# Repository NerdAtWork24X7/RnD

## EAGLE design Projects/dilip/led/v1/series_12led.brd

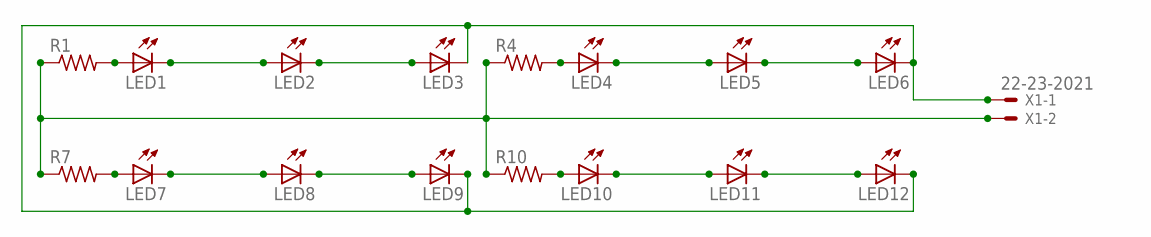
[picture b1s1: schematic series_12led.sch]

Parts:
LED1, LED2, LED3, LED4, LED5, LED6, LED7, LED8, LED9, LED10, LED11, LED12: LED3MM
R1, R4, R7, R10: R-US_0207/10; 0207/10
X1: 22-23-2021

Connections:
unnamed: R1.1, R4.1, R7.1, R10.1, X1.2
unnamed: LED1.A, R1.2
unnamed: LED1.K (C), LED2.A
unnamed: LED2.K (C), LED3.A
unnamed: LED4.A, R4.2
unnamed: LED4.K (C), LED5.A
unnamed: LED5.K (C), LED6.A
unnamed: LED7.A, R7.2
unnamed: LED7.K (C), LED8.A
unnamed: LED8.K (C), LED9.A
unnamed: LED10.A, R10.2
unnamed: LED10.K (C), LED11.A
unnamed: LED11.K (C), LED12.A
unnamed: LED3.K (C), LED6.K (C), LED9.K (C), LED12.K (C), X1.1

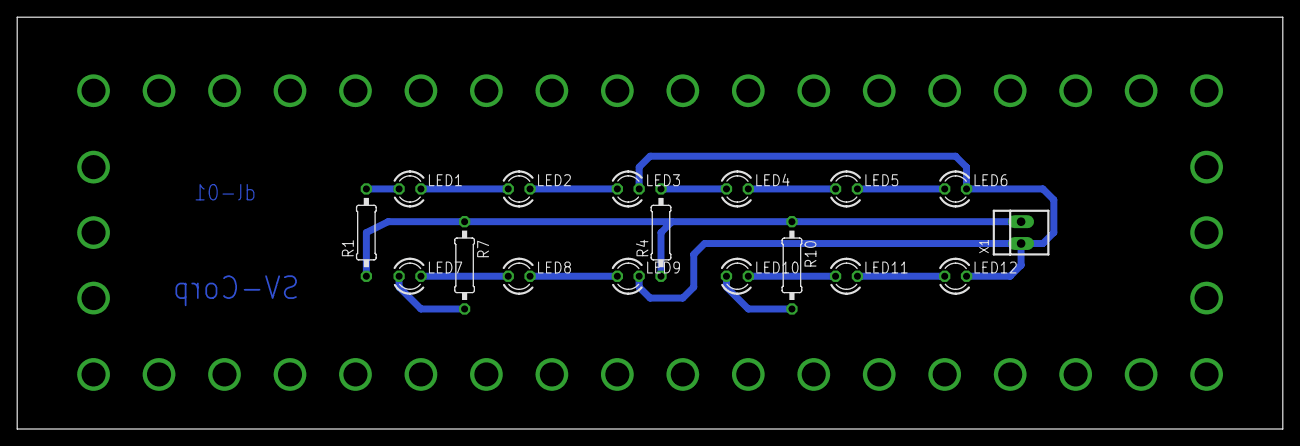
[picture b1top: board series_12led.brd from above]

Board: 2 copper layers, 147.3 x 47.9 mm, 17 parts (0 on the bottom side), 14 nets.

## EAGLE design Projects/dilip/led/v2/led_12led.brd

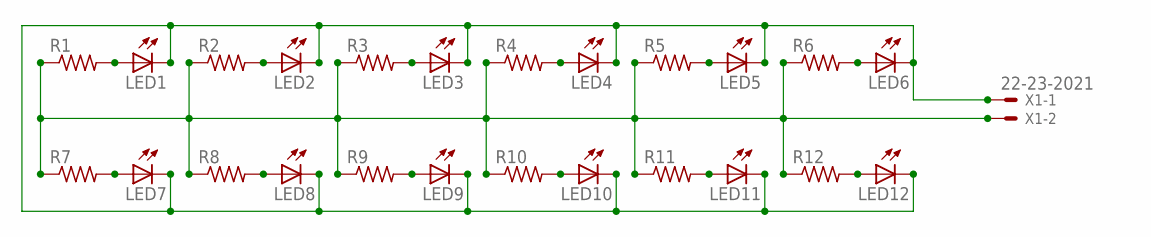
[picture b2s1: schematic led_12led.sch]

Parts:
LED1, LED2, LED3, LED4, LED5, LED6, LED7, LED8, LED9, LED10, LED11, LED12: LED3MM
R1, R2, R3, R4, R5, R6, R7, R8, R9, R10, R11, R12: R-US_0309/12; 0309/12
X1: 22-23-2021

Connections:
unnamed: R1.1, R2.1, R3.1, R4.1, R5.1, R6.1, R7.1, R8.1, R9.1, R10.1, R11.1, R12.1, X1.2
unnamed: LED1.A, R1.2
unnamed: LED2.A, R2.2
unnamed: LED3.A, R3.2
unnamed: LED4.A, R4.2
unnamed: LED5.A, R5.2
unnamed: LED6.A, R6.2
unnamed: LED7.A, R7.2
unnamed: LED8.A, R8.2
unnamed: LED9.A, R9.2
unnamed: LED10.A, R10.2
unnamed: LED11.A, R11.2
unnamed: LED12.A, R12.2
unnamed: LED1.K (C), LED2.K (C), LED3.K (C), LED4.K (C), LED5.K (C), LED6.K (C), LED7.K (C), LED8.K (C), LED9.K (C), LED10.K (C), LED11.K (C), LED12.K (C), X1.1

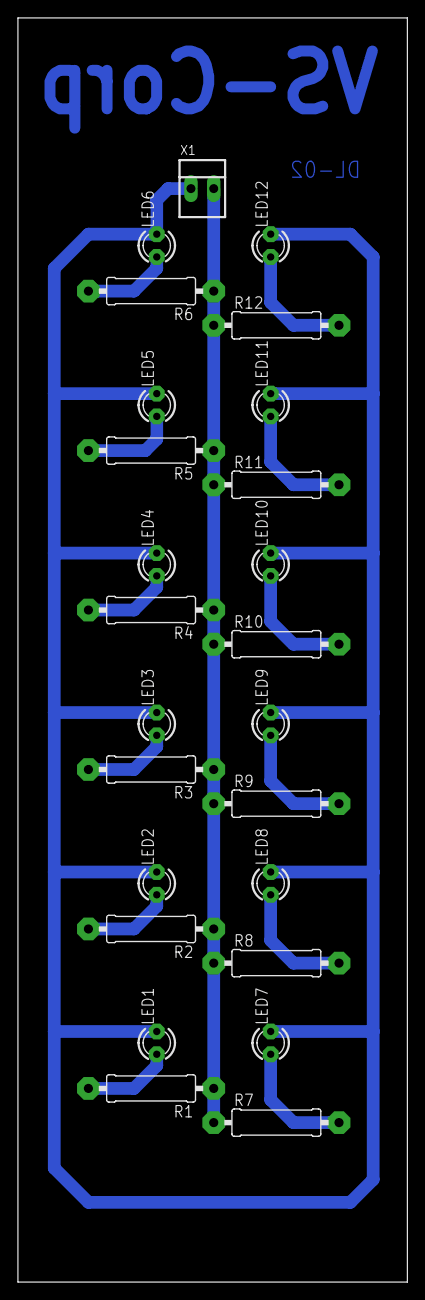
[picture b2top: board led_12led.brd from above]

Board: 2 copper layers, 43.4 x 140.9 mm, 25 parts (0 on the bottom side), 14 nets.

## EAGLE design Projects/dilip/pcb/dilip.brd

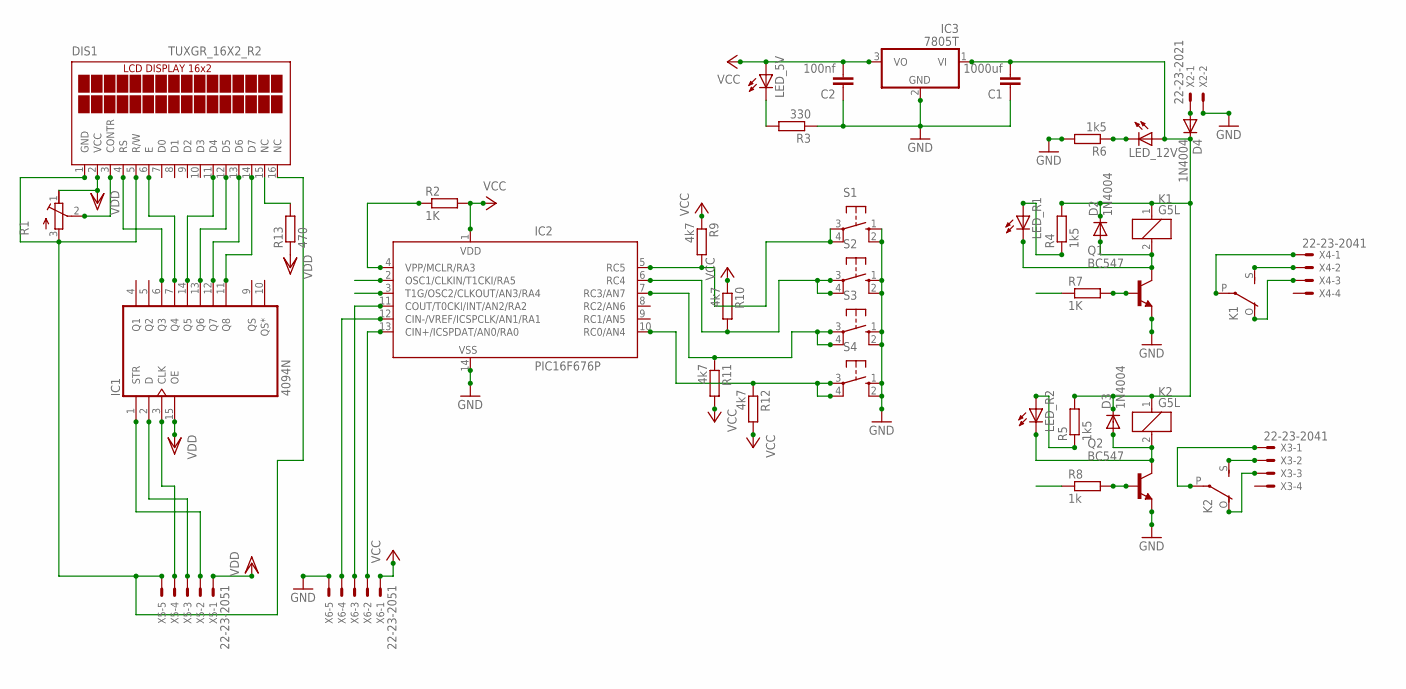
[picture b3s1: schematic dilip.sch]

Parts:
C1: 1000uf; C2.5-6
C2: 100nf; C2.5-6
D2, D3, D4: 1N4004; DO41-10
DIS1: TUXGR_16X2_R2
IC1: 4094N; DIL16
IC2: PIC16F676P; DIL14
IC3: 7805T; TO220H
K1, K2: G5L; G5LE
LED_5V, LED_12V: LED3MM
LED_R1, LED_R2: LED3MM
Q1, Q2: BC547; TO92-EBC
R1: R-TRIMMT93YA; RTRIMT93YA
R2, R7: 1K; 0207/10
R3: 330; 0207/10
R4, R5, R6: 1k5; 0207/10
R8: 1k; 0207/10
R9, R10, R11, R12: 4k7; 0207/10
R13: 470; 0207/10
S1, S2, S3, S4: 40-XX; B3F-40XX
X2: 22-23-2021
X3, X4: 22-23-2041
X5, X6: 22-23-2051

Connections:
E: DIS1.6 (E), IC1.7 (Q4)
GND: C1.1, C2.1, IC2.14 (VSS), IC3.2 (GND), Q1.E, Q2.E, R3.1, R6.2, S1.1 (S), S1.2 (S1), S2.1 (S), S2.2 (S1), S3.1 (S), S3.2 (S1), S4.1 (S), S4.2 (S1), X2.2, X6.5
unnamed: DIS1.3 (CONTR), R1.2 (S)
unnamed: DIS1.11 (D4), IC1.14 (Q5)
unnamed: DIS1.12 (D5), IC1.13 (Q6)
unnamed: DIS1.13 (D6), IC1.12 (Q7)
unnamed: DIS1.14 (D7), IC1.11 (Q8)
unnamed: IC2.11 (COUT/T0CKI/INT/AN2/RA2), X6.3
unnamed: IC2.13 (CIN+/ICSPDAT/AN0/RA0), X6.2
unnamed: IC2.12 (CIN-/VREF/ICSPCLK/AN1/RA1), X6.4
unnamed: IC2.4 (VPP/MCLR/RA3), R2.1
unnamed: Q1.B, R7.2
unnamed: D2.A, K1.2, LED_R1.K (C), Q1.C
unnamed: D3.A, K2.2, LED_R2.K (C), Q2.C
unnamed: Q2.B, R8.2
unnamed: K2.P, X3.1
unnamed: K2.S, X3.2
unnamed: K2.O, X3.3
unnamed: K1.S, X4.2
unnamed: K1.P, X4.1
unnamed: K1.O, X4.3
unnamed: D4.A, X2.1
unnamed: LED_5V.K (C), R3.2
unnamed: LED_R2.A, R5.1
unnamed: IC2.6 (RC4), R10.2, S2.3, S2.4 (P1)
unnamed: LED_R1.A, R4.1
unnamed: IC2.7 (RC3/AN7), R11.1, S3.3, S3.4 (P1)
unnamed: IC2.10 (RC0/AN4), R12.1, S4.3, S4.4 (P1)
unnamed: LED_12V.K (C), R6.1
unnamed: IC1.3 (CLK), X5.4
unnamed: IC1.2 (D), X5.3
unnamed: IC1.1 (STR), X5.2
unnamed: IC2.5 (RC5), R9.2, S1.3, S1.4 (P1)
unnamed: DIS1.15 (NC), R13.2
unnamed: C1.2, D2.C, D3.C, D4.C, IC3.1 (VI), K1.1, K2.1, LED_12V.A, R4.2, R5.2
RELAY1: IC2.2 (OSC1/CLKIN/T1CKI/RA5), R7.1
RELAY2: IC2.3 (T1G/OSC2/CLKOUT/AN3/RA4), R8.1
RS: DIS1.4 (RS), IC1.6 (Q3)
VCC: C2.2, IC2.1 (VDD), IC3.3 (VO), LED_5V.A, R2.2, R9.1, R10.1, R11.2, R12.2, X6.1
VDD: DIS1.2 (VCC), IC1.15 (OE), IC1.16 (VDD), R1.1 (E), R13.1, X5.1
VSS: DIS1.1 (GND), DIS1.5 (R/W), DIS1.16 (NC), IC1.8 (VSS), R1.3 (A), X5.5

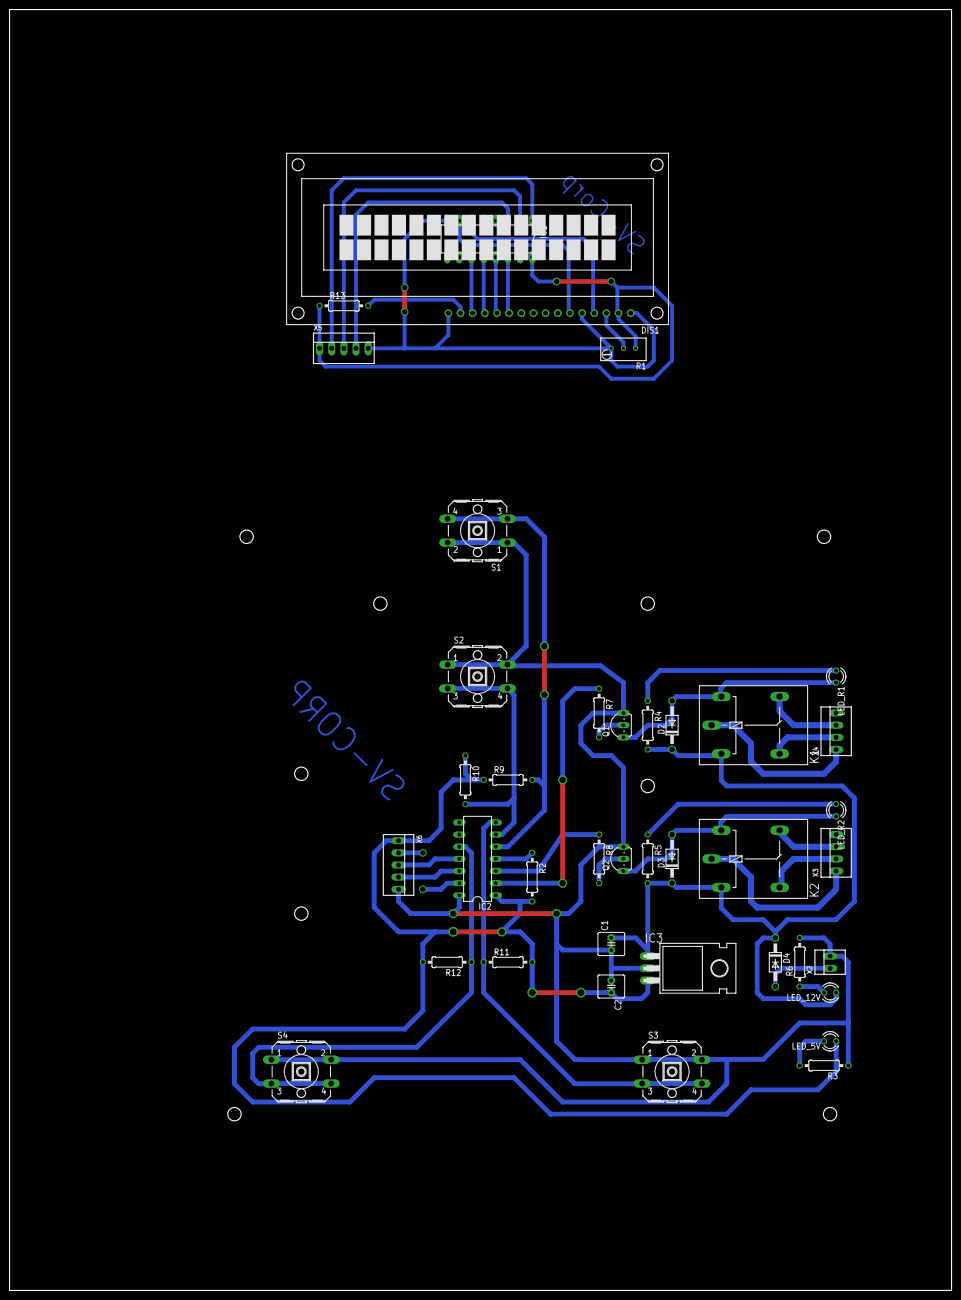
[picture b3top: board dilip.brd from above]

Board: 2 copper layers, 196.8 x 267.6 mm, 39 parts (0 on the bottom side), 41 nets.

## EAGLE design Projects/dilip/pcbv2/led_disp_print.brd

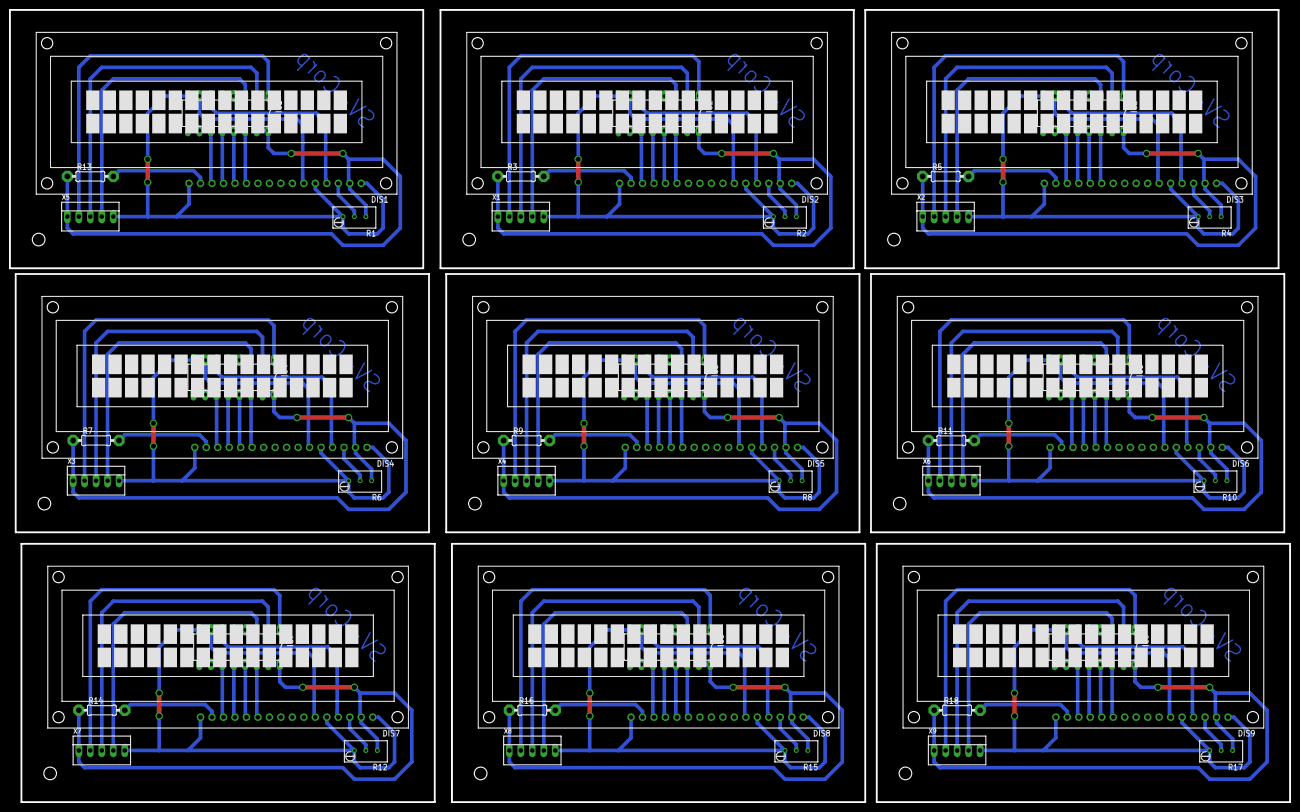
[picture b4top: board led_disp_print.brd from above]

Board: 2 copper layers, 283.2 x 175.3 mm, 45 parts (0 on the bottom side), 117 nets.

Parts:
DIS1, DIS2, DIS3, DIS4, DIS5, DIS6, DIS7, DIS8, DIS9: TUXGR_16X2_R2
IC1, IC2, IC3, IC4, IC5, IC6, IC7, IC8, IC9: 4094N; DIL16
R1, R2, R4, R6, R8, R10, R12, R15, R17: RTRIMT93YA
R3, R5, R7, R9, R11, R13, R14, R16, R18: 470; 0207/10
X1, X2, X3, X4, X5, X6, X7, X8, X9: 22-23-2051

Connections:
E: DIS1.6, IC1.7
E1: DIS2.6, IC2.7
E2: DIS3.6, IC3.7
E3: DIS4.6, IC4.7
E4: DIS5.6, IC5.7
E5: DIS6.6, IC6.7
E6: DIS7.6, IC7.7
E7: DIS8.6, IC8.7
E8: DIS9.6, IC9.7
unnamed: DIS1.3, R1.2
unnamed: DIS1.11, IC1.14
unnamed: DIS1.12, IC1.13
unnamed: DIS1.13, IC1.12
unnamed: DIS1.14, IC1.11
unnamed: DIS2.3, R2.2
unnamed: DIS2.11, IC2.14
unnamed: DIS2.12, IC2.13
unnamed: DIS2.13, IC2.12
unnamed: DIS2.14, IC2.11
unnamed: IC2.3, X1.4
unnamed: IC2.2, X1.3
unnamed: IC2.1, X1.2
unnamed: DIS2.15, R3.2
unnamed: DIS3.3, R4.2
unnamed: DIS3.11, IC3.14
unnamed: DIS3.12, IC3.13
unnamed: DIS3.13, IC3.12
unnamed: DIS3.14, IC3.11
unnamed: IC3.3, X2.4
unnamed: IC3.2, X2.3
unnamed: IC3.1, X2.2
unnamed: DIS3.15, R5.2
unnamed: DIS4.3, R6.2
unnamed: DIS4.11, IC4.14
unnamed: DIS4.12, IC4.13
unnamed: DIS4.13, IC4.12
unnamed: IC1.3, X5.4
unnamed: IC1.2, X5.3
unnamed: IC1.1, X5.2
unnamed: DIS4.14, IC4.11
unnamed: DIS1.15, R13.2
unnamed: IC4.3, X3.4
unnamed: IC4.2, X3.3
unnamed: IC4.1, X3.2
unnamed: DIS4.15, R7.2
unnamed: DIS5.3, R8.2
unnamed: DIS5.11, IC5.14
unnamed: DIS5.12, IC5.13
unnamed: DIS5.13, IC5.12
unnamed: DIS5.14, IC5.11
unnamed: IC5.3, X4.4
unnamed: IC5.2, X4.3
unnamed: IC5.1, X4.2
unnamed: DIS5.15, R9.2
unnamed: DIS6.3, R10.2
unnamed: DIS6.11, IC6.14
unnamed: DIS6.12, IC6.13
unnamed: DIS6.13, IC6.12
unnamed: DIS6.14, IC6.11
unnamed: IC6.3, X6.4
unnamed: IC6.2, X6.3
unnamed: IC6.1, X6.2
unnamed: DIS6.15, R11.2
unnamed: DIS7.3, R12.2
unnamed: DIS7.11, IC7.14
unnamed: DIS7.12, IC7.13
unnamed: DIS7.13, IC7.12
unnamed: DIS7.14, IC7.11
unnamed: IC7.3, X7.4
unnamed: IC7.2, X7.3
unnamed: IC7.1, X7.2
unnamed: DIS7.15, R14.2
unnamed: DIS8.3, R15.2
unnamed: DIS8.11, IC8.14
unnamed: DIS8.12, IC8.13
unnamed: DIS8.13, IC8.12
unnamed: DIS8.14, IC8.11
unnamed: IC8.3, X8.4
unnamed: IC8.2, X8.3
unnamed: IC8.1, X8.2
unnamed: DIS8.15, R16.2
unnamed: DIS9.3, R17.2
unnamed: DIS9.11, IC9.14
unnamed: DIS9.12, IC9.13
unnamed: DIS9.13, IC9.12
unnamed: DIS9.14, IC9.11
unnamed: IC9.3, X9.4
unnamed: IC9.2, X9.3
unnamed: IC9.1, X9.2
unnamed: DIS9.15, R18.2
RS: DIS1.4, IC1.6
RS1: DIS2.4, IC2.6
RS2: DIS3.4, IC3.6
RS3: DIS4.4, IC4.6
RS4: DIS5.4, IC5.6
RS5: DIS6.4, IC6.6
RS6: DIS7.4, IC7.6
RS7: DIS8.4, IC8.6
RS8: DIS9.4, IC9.6
VDD: DIS1.2, IC1.15, IC1.16, R1.1, R13.1, X5.1
VDD1: DIS2.2, IC2.15, IC2.16, R2.1, R3.1, X1.1
VDD2: DIS3.2, IC3.15, IC3.16, R4.1, R5.1, X2.1
VDD3: DIS4.2, IC4.15, IC4.16, R6.1, R7.1, X3.1
VDD4: DIS5.2, IC5.15, IC5.16, R8.1, R9.1, X4.1
VDD5: DIS6.2, IC6.15, IC6.16, R10.1, R11.1, X6.1
VDD6: DIS7.2, IC7.15, IC7.16, R12.1, R14.1, X7.1
VDD7: DIS8.2, IC8.15, IC8.16, R15.1, R16.1, X8.1
VDD8: DIS9.2, IC9.15, IC9.16, R17.1, R18.1, X9.1
VSS: DIS1.1, DIS1.5, DIS1.16, IC1.8, R1.3, X5.5
VSS1: DIS2.1, DIS2.5, DIS2.16, IC2.8, R2.3, X1.5
VSS2: DIS3.1, DIS3.5, DIS3.16, IC3.8, R4.3, X2.5
VSS3: DIS4.1, DIS4.5, DIS4.16, IC4.8, R6.3, X3.5
VSS4: DIS5.1, DIS5.5, DIS5.16, IC5.8, R8.3, X4.5
VSS5: DIS6.1, DIS6.5, DIS6.16, IC6.8, R10.3, X6.5
VSS6: DIS7.1, DIS7.5, DIS7.16, IC7.8, R12.3, X7.5
VSS7: DIS8.1, DIS8.5, DIS8.16, IC8.8, R15.3, X8.5
VSS8: DIS9.1, DIS9.5, DIS9.16, IC9.8, R17.3, X9.5
